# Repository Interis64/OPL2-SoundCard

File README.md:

# OPL2-SoundCard
 Yamaha OPL2 FM Synthesis sound card for Interis 64

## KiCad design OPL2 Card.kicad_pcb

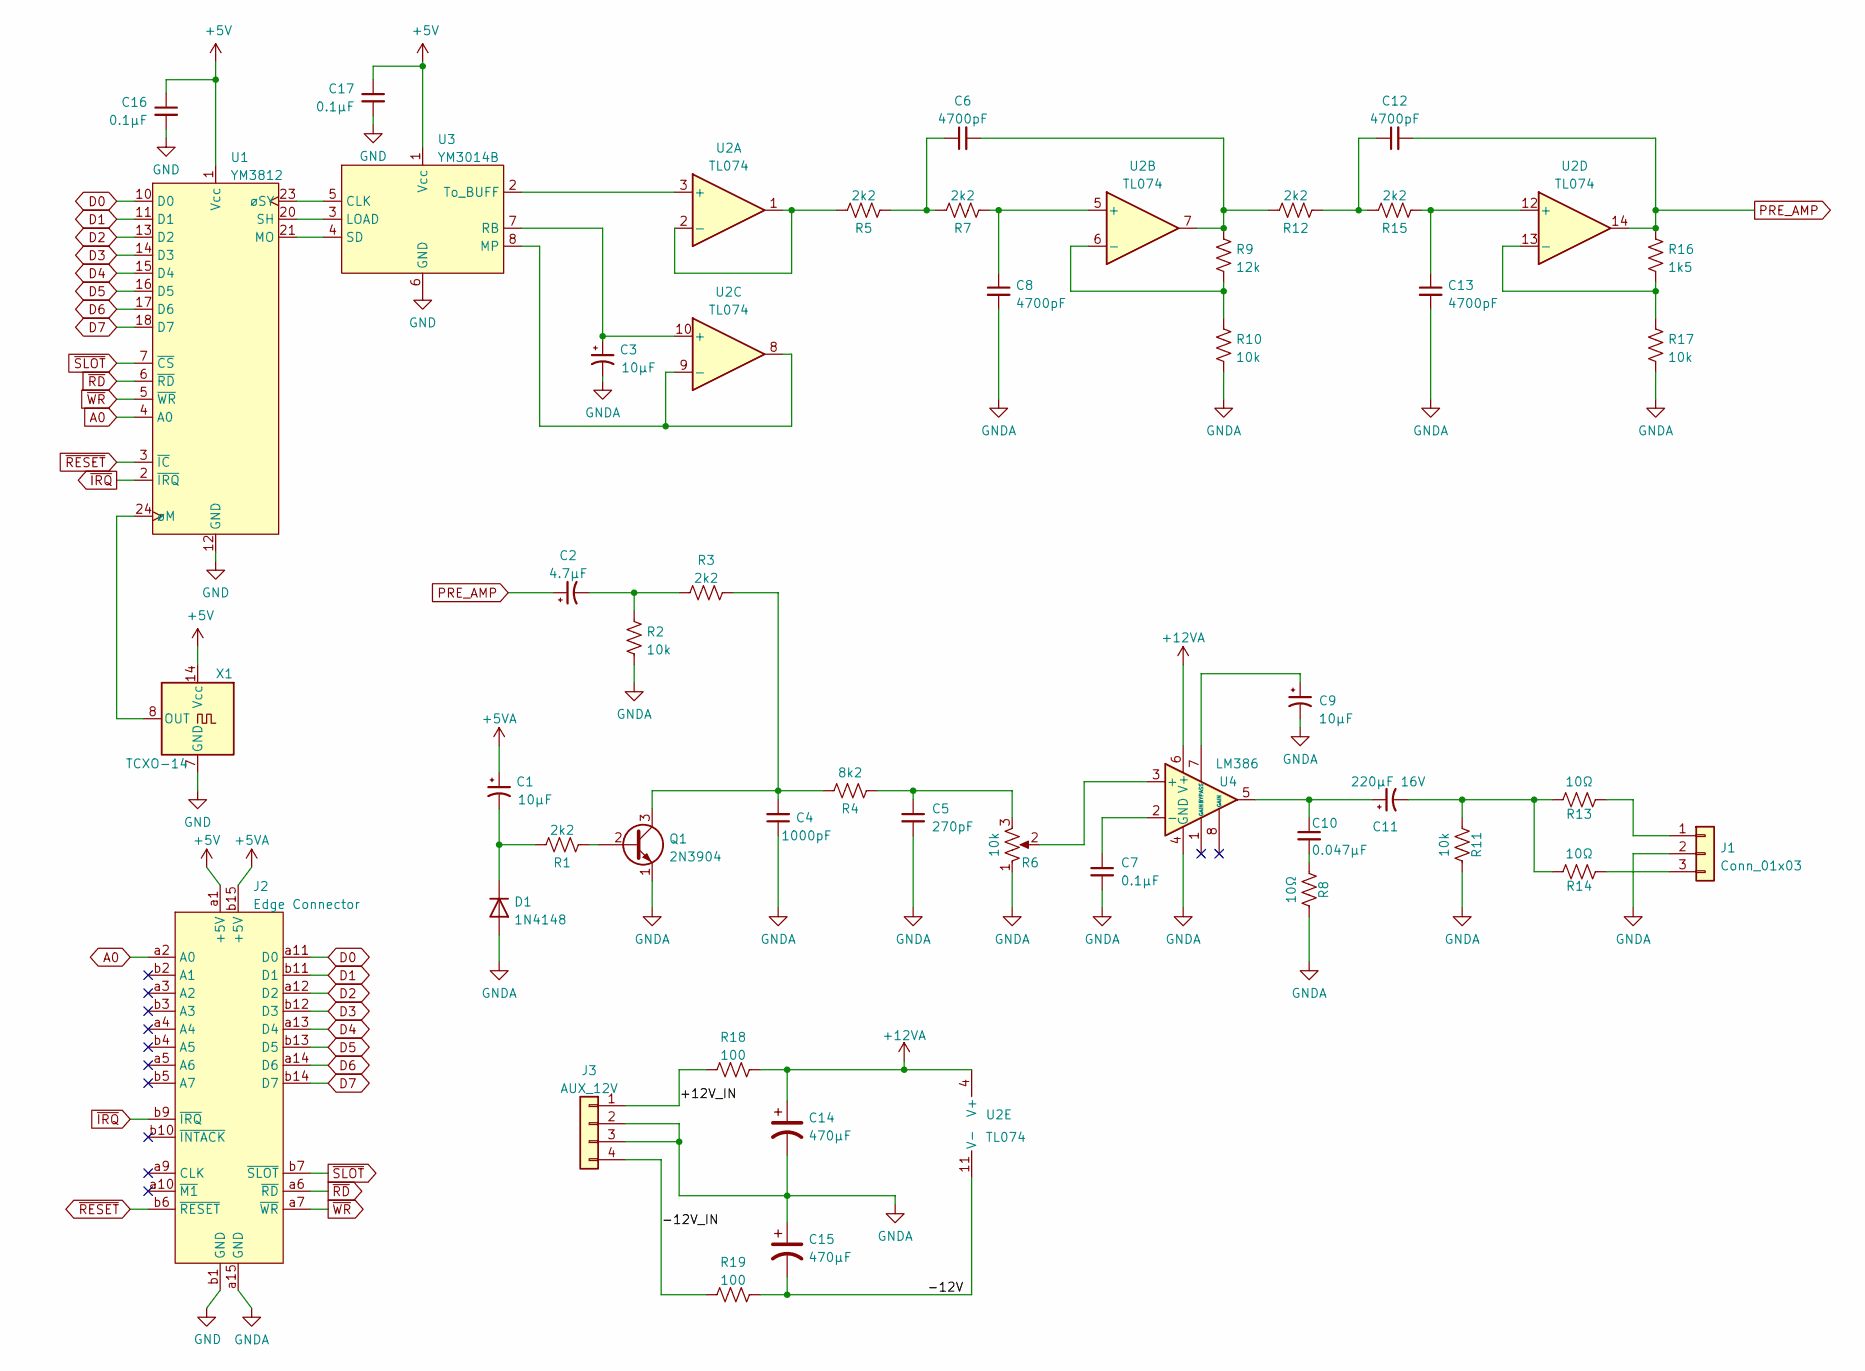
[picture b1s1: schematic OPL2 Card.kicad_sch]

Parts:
C1, C3: 10µF; CP_Radial_D5.0mm_P2.50mm
C2: 4.7µF; CP_Radial_D5.0mm_P2.50mm
C4: 1000pF; C_Disc_D3.8mm_W2.6mm_P2.50mm; Mouser 581-AR211C102K4R
C5: 270pF; C_Disc_D3.8mm_W2.6mm_P2.50mm; Mouser 594-S271K43SL0N6TK5R
C6, C8, C12, C13: 4700pF; C_Disc_D3.8mm_W2.6mm_P2.50mm
C7, C16, C17: 0.1µF; C_Disc_D5.0mm_W2.5mm_P2.50mm; Mouser 581-AR215C104K4R
C9: 10µF; CP_Radial_D5.0mm_P2.50mm; Mouser 581-TAP106M025CRW
C10: 0.047µF; C_Disc_D5.0mm_W2.5mm_P2.50mm; Mouser 581-AR215C473K4R
C11: 220µF 16V; CP_Radial_D6.3mm_P2.50mm; Mouser 647-TVX1C221MAD
C14, C15: 470µF; CP_Radial_D12.5mm_P5.00mm
D1: 1N4148; D_DO-35_SOD27_P7.62mm_Horizontal
J1: Conn_01x03; PinHeader_1x03_P2.54mm_Horizontal
J2: Edge Connector; BUS_Interis
J3: AUX_12V; PinHeader_1x04_P2.54mm_Horizontal
Q1: 2N3904; TO-92_Inline
R1, R3, R5, R7, R12, R15: 2k2; R_Axial_DIN0207_L6.3mm_D2.5mm_P7.62mm_Horizontal
R2, R10, R17: 10k; R_Axial_DIN0207_L6.3mm_D2.5mm_P7.62mm_Horizontal
R4: 8k2; R_Axial_DIN0207_L6.3mm_D2.5mm_P7.62mm_Horizontal; Mouser 291-8.2K-RC
R6: 10k; PinHeader_1x03_P2.54mm_Horizontal; Mouser 652-91A1A-B24-D15L
R8, R13, R14: 10Ω; R_Axial_DIN0207_L6.3mm_D2.5mm_P7.62mm_Horizontal; Mouser 291-10-RC
R9: 12k; R_Axial_DIN0207_L6.3mm_D2.5mm_P7.62mm_Horizontal
R11: 10k; R_Axial_DIN0207_L6.3mm_D2.5mm_P7.62mm_Horizontal; Mouser 291-10K-RC
R16: 1k5; R_Axial_DIN0207_L6.3mm_D2.5mm_P7.62mm_Horizontal
R18, R19: 100; R_Axial_DIN0207_L6.3mm_D2.5mm_P10.16mm_Horizontal
U1: YM3812; DIP-24_W15.24mm
U2: TL074; DIP-14_W7.62mm
U3: YM3014B; DIP-8_W7.62mm
U4: LM386; DIP-8_W7.62mm
X1: TCXO-14; Oscillator_DIP-14

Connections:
+5V: C16.1, C17.1, J2.a1 (+5V), U1.1 (Vcc), U3.1 (Vcc), X1.14 (Vcc)
+5VA: C1.1, J2.b15 (+5V)
+12VA: C14.1, R18.2, U2.4 (V+), U4.6 (V+)
/+12V_IN: J3.1 (+12V), R18.1
/-12V: C15.2, R19.2, U2.11 (V-)
/-12V_IN: J3.4, R19.1
A0: J2.a2 (A0), U1.4 (A0)
D0: J2.a11 (D0), U1.10 (D0)
D1: J2.b11 (D1), U1.11 (D1)
D2: J2.a12 (D2), U1.13 (D2)
D3: J2.b12 (D3), U1.14 (D3)
D4: J2.a13 (D4), U1.15 (D4)
D5: J2.b13 (D5), U1.16 (D5)
D6: J2.a14 (D6), U1.17 (D6)
D7: J2.b14 (D7), U1.18 (D7)
GND: C16.2, C17.2, J2.b1 (GND), U1.12 (GND), U3.6 (GND), X1.7 (GND)
GNDA: C3.2, C4.1, C5.2, C7.2, C8.2, C9.2, C13.2, C14.2, C15.1, D1.2 (A), J1.2, J2.a15 (GND), J3.2, J3.3, Q1.1 (E), R2.2, R6.1, R8.2, R10.2, R11.2, R17.2, U4.4 (GND)
unnamed: C2.2, R2.1, R3.1
unnamed: C5.1, R4.1, R6.3
unnamed: C6.1, R5.2, R7.1
unnamed: C6.2, R9.1, R12.1, U2.7
unnamed: C10.1, C11.1, U4.5
unnamed: C10.2, R8.1
unnamed: C11.2, R11.1, R13.2, R14.2
unnamed: C12.1, R12.2, R15.1
unnamed: C1.2, D1.1 (K), R1.1
unnamed: J1.1, R13.1
unnamed: J1.3, R14.1
unnamed: Q1.2 (B), R1.2
unnamed: C4.2, Q1.3 (C), R3.2, R4.2
unnamed: U1.21 (MO), U3.4 (SD)
unnamed: U1.20 (SH), U3.3 (LOAD)
unnamed: U1.24 (øM), X1.8 (OUT)
unnamed: U1.23 (øSY), U3.5 (CLK)
unnamed: U2.3 (+), U3.2 (To_BUFF)
unnamed: R5.1, U2.1, U2.2 (-)
unnamed: C8.1, R7.2, U2.5 (+)
unnamed: R9.2, R10.1, U2.6 (-)
unnamed: C3.1, U2.10 (+), U3.7 (RB)
unnamed: U2.8, U2.9 (-), U3.8 (MP)
unnamed: C13.1, R15.2, U2.12 (+)
unnamed: R16.2, R17.1, U2.13 (-)
unnamed: R6.2, U4.3 (+)
unnamed: C7.1, U4.2 (-)
unnamed: C9.1, U4.7 (BYPASS)
PRE_AMP: C2.1, C12.2, R16.1, U2.14
~IRQ: J2.b9 (~IRQ), U1.2 (~IRQ)
~RD: J2.a6 (~RD), U1.6 (~RD)
~RESET: J2.b6 (~RESET), U1.3 (~IC)
~SLOT: J2.b7 (~SLOT), U1.7 (~CS)
~WR: J2.a7 (~WR), U1.5 (~WR)

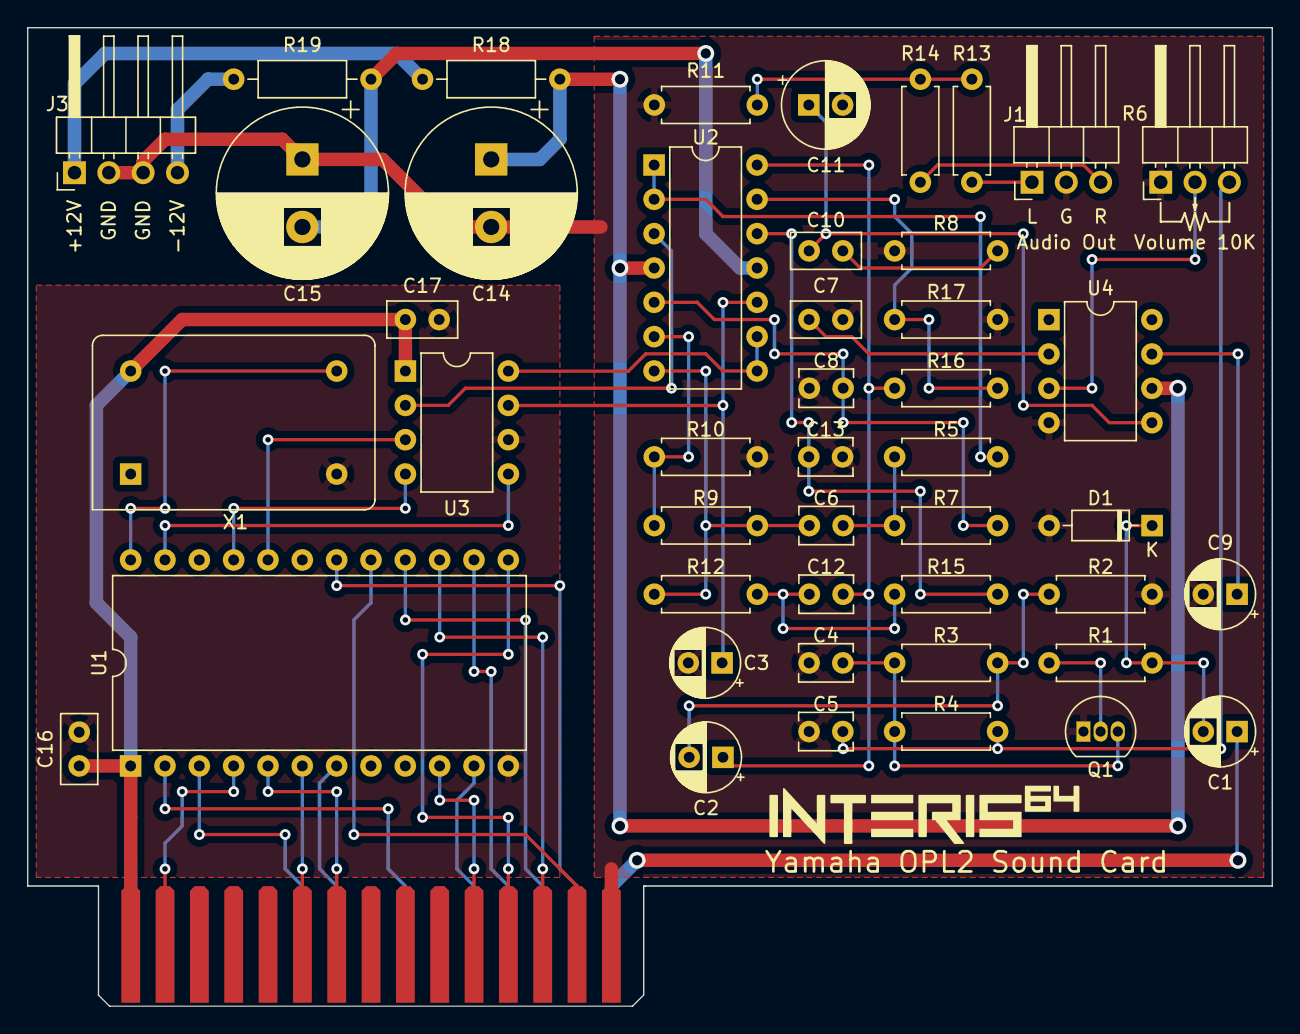
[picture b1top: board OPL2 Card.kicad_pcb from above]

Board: 2 copper layers, 92.1 x 72.4 mm, 46 parts (0 on the bottom side), 51 nets.
